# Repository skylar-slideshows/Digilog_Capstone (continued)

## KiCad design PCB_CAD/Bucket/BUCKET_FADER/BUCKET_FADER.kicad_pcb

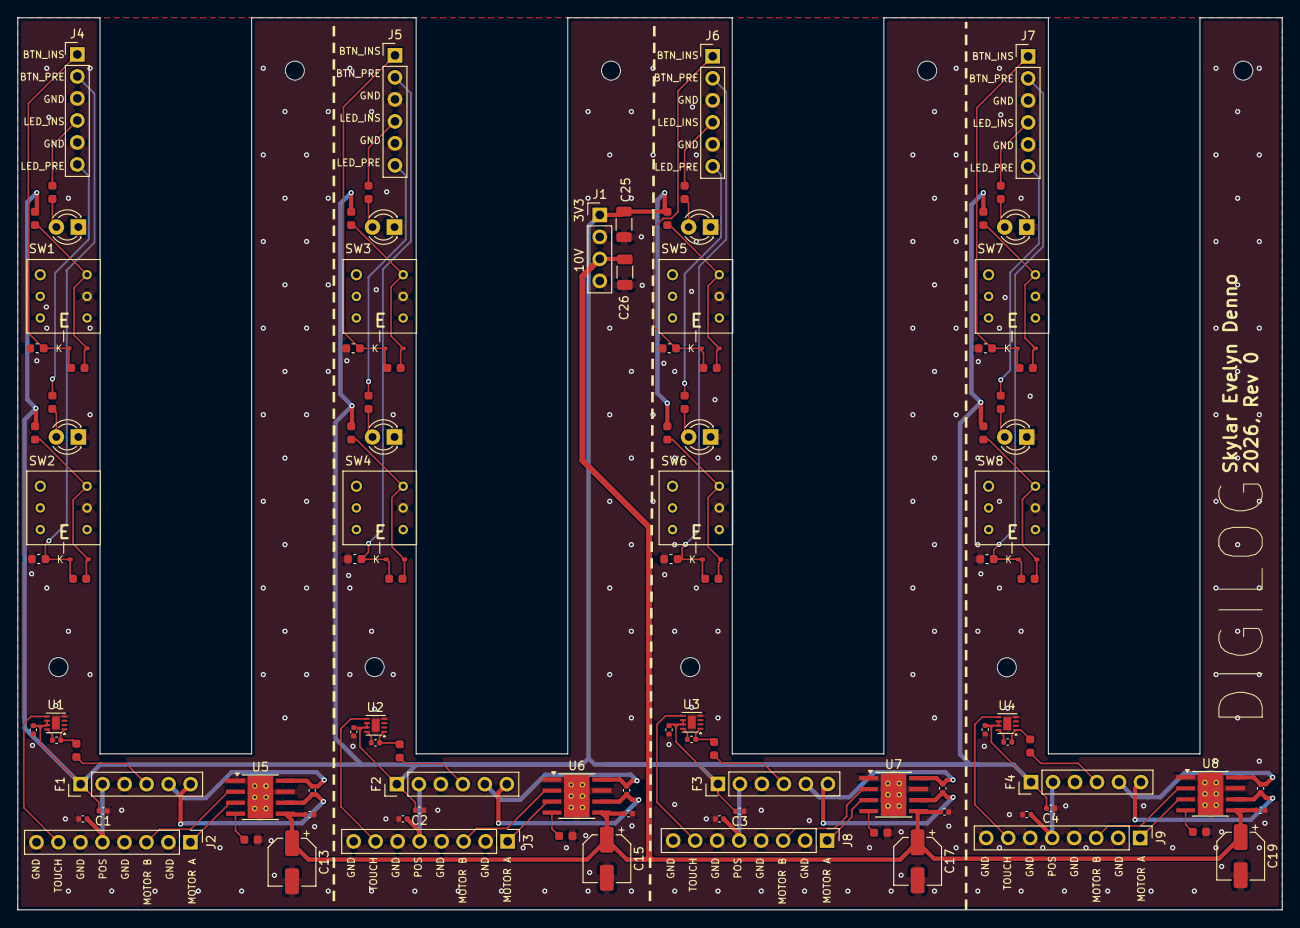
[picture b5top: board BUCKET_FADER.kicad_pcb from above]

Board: 4 copper layers, 146.0 x 103.0 mm, 123 parts (0 on the bottom side), 75 nets.

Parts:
C1, C2, C3, C4, C5, C6, C7, C8, C14, C16, C18, C20, C35, C36, C37, C38: 100n; C_0402_1005Metric
C9, C10, C11, C12, C21, C22, C23, C24: 10n; C_0402_1005Metric
C13, C15, C17, C19: 22u; CP_Elec_5x5.4
C25, C26: 10u; C_1206_3216Metric
C27, C28, C29, C30, C31, C32, C33, C34: 1u; C_0603_1608Metric
D1, D2, D3, D4, D9, D10, D11, D12: 1N4148; D_SOD-323
D5, D6, D7, D8, D13, D14, D15, D16: LED; LED_D3.0mm_FlatTop
F1, F2, F3, F4: Alps_RSA0N11M9; PinHeader_1x06_P2.54mm_Vertical
H1, H2, H3, H4, H5, H6, H7, H8: MountingScrew; MountingHole_2.2mm_M2
J1: POW; PinHeader_1x04_P2.54mm_Vertical
J2: F0_MCU; PinHeader_1x08_P2.54mm_Vertical
J3: F1_MCU; PinHeader_1x08_P2.54mm_Vertical
J4: F0_BTN; PinHeader_1x06_P2.54mm_Vertical
J5: F1_BTN; PinHeader_1x06_P2.54mm_Vertical
J6: F2_BTN; PinHeader_1x06_P2.54mm_Vertical
J7: F3_BTN; PinHeader_1x06_P2.54mm_Vertical
J8: F2_MCU; PinHeader_1x08_P2.54mm_Vertical
J9: F3_MCU; PinHeader_1x08_P2.54mm_Vertical
R1, R2, R3, R4: 10k; R_0603_1608Metric
R5, R6, R7, R8: 82k; R_0603_1608Metric
R9, R10, R11, R12, R21, R22, R23, R24: 47k; R_0603_1608Metric
R13, R14, R15, R16, R25, R26, R27, R28: 15k; R_0603_1608Metric
R17, R18, R19, R20, R29, R30, R31, R32: 6.8k; R_0603_1608Metric
SW1, SW3, SW5, SW7: C0_B10; TL2201EEZB
SW2, SW4, SW6, SW8: C0_B11; TL2201EEZB
U1, U2, U3, U4: AT42QT1011-M; DFN-8-1EP_2x2mm_P0.5mm_EP0.9x1.5mm
U5, U6, U7, U8: DRV8871DDA; Texas_HTSOP-8-1EP_3.9x4.9mm_P1.27mm_EP2.95x4.9mm_Mask2.4x3.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

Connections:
+3V3: C1.2, C2.2, C3.2, C4.2, C5.2, C6.2, C7.2, C8.2, C25.1, F1.1, F2.1, F3.1, F4.1, J1.1, R9.1, R10.1, R11.1, R12.1, R21.1, R22.1, R23.1, R24.1, U1.6 (SYNC), U1.7 (VDD), U2.6 (SYNC), U2.7 (VDD), U3.6 (SYNC), U3.7 (VDD), U4.6 (SYNC), U4.7 (VDD)
+10V: C13.1, C14.2, C15.1, C16.2, C17.1, C18.2, C19.1, C20.2, C26.1, J1.3, U5.5 (VM), U6.5 (VM), U7.5 (VM), U8.5 (VM)
/F0_MotA: C21.1, F1.5 (A), U5.8 (OUT2)
/F0_MotB: C21.2, F1.6 (B), U5.6 (OUT1)
/F0_Touch: F1.4 (T), R1.2
/F1_MotA: C22.1, F2.5 (A), U6.8 (OUT2)
/F1_MotB: C22.2, F2.6 (B), U6.6 (OUT1)
/F1_Touch: F2.4 (T), R2.2
/F2_MotA: C23.1, F3.5 (A), U7.8 (OUT2)
/F2_MotB: C23.2, F3.6 (B), U7.6 (OUT1)
/F2_Touch: F3.4 (T), R3.2
/F3_MotA: C24.1, F4.5 (A), U8.8 (OUT2)
/F3_MotB: C24.2, F4.6 (B), U8.6 (OUT1)
/F3_Touch: F4.4 (T), R4.2
F0_BTN_INS: C27.1, D1.1 (K), J4.1, R13.2
F0_BTN_PRE: C28.1, D2.1 (K), J4.2, R14.2
F0_LED_INS: J4.4, R17.2
F0_LED_PRE: J4.6, R18.2
F0_MA: J2.1, U5.3 (IN1)
F0_MB: J2.3, U5.2 (IN2)
F0_POS: C35.2, F1.2, J2.5
F0_TOUCH: J2.7, U1.5 (OUT)
F1_BTN_INS: C29.1, D3.1 (K), J5.1, R15.2
F1_BTN_PRE: C30.1, D4.1 (K), J5.2, R16.2
F1_LED_INS: J5.4, R19.2
F1_LED_PRE: J5.6, R20.2
F1_MA: J3.1, U6.3 (IN1)
F1_MB: J3.3, U6.2 (IN2)
F1_POS: C36.2, F2.2, J3.5
F1_TOUCH: J3.7, U2.5 (OUT)
F2_BTN_INS: C31.1, D9.1 (K), J6.1, R25.2
F2_BTN_PRE: C32.1, D10.1 (K), J6.2, R26.2
F2_LED_INS: J6.4, R29.2
F2_LED_PRE: J6.6, R30.2
F2_MA: J8.1, U7.3 (IN1)
F2_MB: J8.3, U7.2 (IN2)
F2_POS: C37.2, F3.2, J8.5
F2_TOUCH: J8.7, U3.5 (OUT)
F3_BTN_INS: C33.1, D11.1 (K), J7.1, R27.2
F3_BTN_PRE: C34.1, D12.1 (K), J7.2, R28.2
F3_LED_INS: J7.4, R31.2
F3_LED_PRE: J7.6, R32.2
F3_MA: J9.1, U8.3 (IN1)
F3_MB: J9.3, U8.2 (IN2)
F3_POS: C38.2, F4.2, J9.5
F3_TOUCH: J9.7, U4.5 (OUT)
GND: C1.1, C2.1, C3.1, C4.1, C5.1, C6.1, C7.1, C8.1, C13.2, C14.1, C15.2, C16.1, C17.2, C18.1, C19.2, C20.1, C25.2, C26.2, C27.2, C28.2, C29.2, C30.2, C31.2, C32.2, C33.2, C34.2, C35.1, C36.1, C37.1, C38.1, D5.1 (K), D6.1 (K), D7.1 (K), D8.1 (K), D13.1 (K), D14.1 (K), D15.1 (K), D16.1 (K), F1.3, F2.3, F3.3, F4.3, J1.2, J1.4, J2.2, J2.4, J2.6, J2.8, J3.2, J3.4, J3.6, J3.8, J4.3, J4.5, J5.3, J5.5, J6.3, J6.5, J7.3, J7.5, J8.2, J8.4, J8.6, J8.8, J9.2, J9.4, J9.6, J9.8, R5.2, R6.2, R7.2, R8.2, SW1.2 (B), SW2.2 (B), SW3.2 (B), SW4.2 (B), SW5.2 (B), SW6.2 (B), SW7.2 (B), SW8.2 (B), U1.4 (VSS), U1.9 (VSS), U2.4 (VSS), U2.9 (VSS), U3.4 (VSS), U3.9 (VSS), U4.4 (VSS), U4.9 (VSS), U5.1 (GND), U5.7 (GND), U5.9 (GND), U6.1 (GND), U6.7 (GND), U6.9 (GND), U7.1 (GND), U7.7 (GND), U7.9 (GND), U8.1 (GND), U8.7 (GND), U8.9 (GND)
unnamed: D1.2 (A), R9.2, R13.1, SW1.3 (C)
unnamed: D2.2 (A), R10.2, R14.1, SW2.3 (C)
unnamed: D3.2 (A), R11.2, R15.1, SW3.3 (C)
unnamed: D4.2 (A), R12.2, R16.1, SW4.3 (C)
unnamed: D5.2 (A), R17.1
unnamed: D6.2 (A), R18.1
unnamed: D7.2 (A), R19.1
unnamed: D8.2 (A), R20.1
unnamed: D9.2 (A), R21.2, R25.1, SW5.3 (C)
unnamed: D10.2 (A), R22.2, R26.1, SW6.3 (C)
unnamed: D11.2 (A), R23.2, R27.1, SW7.3 (C)
unnamed: D12.2 (A), R24.2, R28.1, SW8.3 (C)
unnamed: D13.2 (A), R29.1
unnamed: D14.2 (A), R30.1
unnamed: D15.2 (A), R31.1
unnamed: D16.2 (A), R32.1
unnamed: C9.2, U1.8 (SNS)
unnamed: C9.1, R1.1, U1.1 (SNSK)
unnamed: C10.2, U2.8 (SNS)
unnamed: C10.1, R2.1, U2.1 (SNSK)
unnamed: C11.2, U3.8 (SNS)
unnamed: C11.1, R3.1, U3.1 (SNSK)
unnamed: C12.2, U4.8 (SNS)
unnamed: C12.1, R4.1, U4.1 (SNSK)
unnamed: R5.1, U5.4 (ILIM)
unnamed: R6.1, U6.4 (ILIM)
unnamed: R7.1, U7.4 (ILIM)
unnamed: R8.1, U8.4 (ILIM)

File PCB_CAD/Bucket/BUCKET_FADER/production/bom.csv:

Designator,Footprint,Quantity,Value,LCSC Part #
"C1, C14, C16, C18, C2, C20, C3, C35, C36, C37, C38, C4, C5, C6, C7, C8",0402,16,100n,C1525
"C10, C11, C12, C21, C22, C23, C24, C9",0402,8,10n,C1524
"C13, C15, C17, C19",CP_Elec_5x5.4,4,22u,C15848
"C25, C26",1206,2,10u,C1849
"C27, C28, C29, C30, C31, C32, C33, C34",0603,8,1u,C15849
"D1, D10, D11, D12, D2, D3, D4, D9",D_SOD-323,8,1N4148,C2128
"D13, D14, D15, D16, D5, D6, D7, D8",LED_D3.0mm_FlatTop,8,LED,dnp
"F1, F2, F3, F4",PinHeader_1x06_P2.54mm_Vertical,4,Alps_RSA0N11M9,dnp
J1,PinHeader_1x04_P2.54mm_Vertical,1,POW,dnp
J2,PinHeader_1x08_P2.54mm_Vertical,1,F0_MCU,dnp
J3,PinHeader_1x08_P2.54mm_Vertical,1,F1_MCU,dnp
J4,PinHeader_1x06_P2.54mm_Vertical,1,F0_BTN,dnp
J5,PinHeader_1x06_P2.54mm_Vertical,1,F1_BTN,dnp
J6,PinHeader_1x06_P2.54mm_Vertical,1,F2_BTN,dnp
J7,PinHeader_1x06_P2.54mm_Vertical,1,F3_BTN,dnp
J8,PinHeader_1x08_P2.54mm_Vertical,1,F2_MCU,dnp
J9,PinHeader_1x08_P2.54mm_Vertical,1,F3_MCU,dnp
"R1, R2, R3, R4",0603,4,10k,C15401
"R10, R11, R12, R21, R22, R23, R24, R9",0603,8,47k,C25600
"R13, R14, R15, R16, R25, R26, R27, R28",0603,8,15k,C22809
"R17, R18, R19, R20, R29, R30, R31, R32",0603,8,6.8k,C23212
"R5, R6, R7, R8",0603,4,82k,C1275
"SW1, SW3, SW5, SW7",TL2201EEZB,4,C0_B10,dnp
"SW2, SW4, SW6, SW8",TL2201EEZB,4,C0_B11,dnp
"U1, U2, U3, U4",DFN-8-1EP_2x2mm_P0.5mm_EP0.9x1.5mm,4,AT42QT1011-M,C2652045
"U5, U6, U7, U8",Texas_HTSOP-8-1EP_3.9x4.9mm_P1.27mm_EP2.95x4.9mm_Mask2.4x3.1mm_ThermalVias,4,DRV8871DDA,C75864
